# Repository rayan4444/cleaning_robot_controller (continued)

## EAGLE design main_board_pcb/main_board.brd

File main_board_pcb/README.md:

# Robodeck Main Board

## Description
Main controller for motors, sensors and other peripherals. Features:
- 1x STM32F407 100pin microcontroller
- 6x 24V-3A motor drivers with fault detection, current sensing and current limiting
    - 2 with encoder lines
    - 4 simple
- 2x 24V- 10A motor drivers with fault detection, current sensing and current limiting
- 2x N-MOSFET Switches (up to 2A)
- 1x Hall effect current sensor on main input
- 1x Input voltage measurement
- 1x UART breakout
- 1x SPI breakout
- 1x I2C breakout
- 3x pressure sensor connectors
- 1x on board temperature and humidity sensor
- 2x connectors for external temperature sensors
- 2x Cliff sensor connectors
- 1x front gap sensor connector
- 2x 5V servo connectors
- 1x SMBUS BMS connector
- 1x RS-485 transceiver
- 2x bumpers connectors
- 1x SWD programming and debug header
- 1x UI board connector
- 2x USB outputs with power and data (up to 2.5A, data can be disconnected from one of the ports)
- 2x optional breakouts for Brushless ESC (share signal with high power motor drivers)
- 1x spare port breakout

## Hardware connections
Microcontroller

|STM32 Pin | Peripheral| Signal|Notes|Test results|
|:---:|:---:|:---:|:---:|:---:|
|PC9 |**TIM3_CH4**|DRIVE1_A |PWM||
|PC12| GPIO OUT |DRIVE1_B||
|PD13| EXTI_13|DRIVE1_FAULT||  
|PB0| ADC1_CH8||DRIVE1_CURRENT||
|PB2| GPIO OUT| MOTOR_SLEEP |also BOOT1 pin|
|PC8|**TIM3_CH3**|DRIVE2_A |PWM|
|PC11|GPIO OUT|DRIVE2_B||
|PD12|EXTI_12|DRIVE2_FAULT||
|PB1| ADC_CH9|DRIVE2_CURRENT||
|PC6|**TIM3_CH1**|PRESSURE_PUMP_A|PWM|
|PA8|GPIO OUT|PRESSURE_PUMP_B||
|PD10|EXTI_10|PRESSURE_PUMP_FAULT||
|PC7|**TIM3_CH2**|CENTRAL_BRUSH_A|PWM|
|PC10|GPIO OUT|CENTRAL_BRUSH_B||
|PD11|EXTI_11|CENTRAL_BRUSH_FAULT||
|PC5|ADC1_CH5|CENTRAL_BRUSH_CURRENT||
|PE14|**TIM1_CH4**|SCRUBBER1_A|PWM|
|PE15|GPIO OUT|SCRUBBER1_B||
|PB15|EXTI_15|SCRUBBER1_FAULT||
|PA3|ADC1_CH3|SCRUBBER1_CURRENT|PWM|
|PE13|**TIM1_CH3**|SCRUBBER2_A|PWM|
|PE12|GPIO OUT|SCRUBBER2_B||   
|PB14|EXTI_14|SCRUBBER2_FAULT||
|PC4|ADC1_CH14|SCRUBBER2_CURRENT||
|PD1|EXTI_1|BUMPER1||
|PD0|EXTI_0|BUMPER2||
|PD8|EXTI_8|ENCODER1||
|PD9|EXTI_9|ENCODER2||   
|PD15|**TIM4_CH4**|SERVO1|PWM|
|PD14|**TIM4_CH3**|SERVO2|PWM|
|PB8|GPIO OUT|SOLENOID1||
|PB9|GPIO OUT|SOLENOID2||
|PE9|**TIM1_CH1**|STAINING_FAN1_A||
|PE8|GPIO OUT|STAINING_FAN1_B||
|PE6|EXTI_6|STAINING_FAN1_FAULT||
|PE11|**TIM1_CH2**|STAINING_FAN2_A||
|PE10|GPIO OUT|STAINING_FAN2_B||
|PE7|EXTI_7|STAINING_FAN2_FAULT||
|PB6|I2C1_SCL|SCL||
|PB7|i2C1_SDA|SDA||
|PD6|USART2_RX|RS485_RX||
|PD5|USART2_TX|RS485_TX||
|PE0|GPIO OUT|RS485_DIR||
|PB4|SPI1_MISO|MISO||
|PB5|SPI1_MOSI|MOSI||
|PD7|GPIO OUT|CS||
|PB3|SPI1_SCK|SCK||
|PA12|USB_DP|D_P||
|PA11|USB_DN|D_N||
|PA13|SWDIO|SWDIO||
|PA14|SWCLK|SWCLK||
|PA9|USART1_TX|USART1_TX||    
|PA10|USART1_RX|USART1_RX||
|PB11|I2C2_SDA|SMBUS_SDA||
|PB10|I2C2_SCL|SMBUS_SCL||     
|PB12|I2C2_SMBA|SMBUS_ALERT||
|PAB13|GPIO OUT|SMBUS_IO||
|PC2|ADC1_CH12|CLIFF1_OUT||
|PC3|ADC1_CH13|CLIFF2_OUT||
|PC0|ADC1_CH10|GAP_SENSE_1||
|PC1|ADC1_CH11|GAP_SENSE_2||
|PD4|EXTI_4|ONxOFF|from UI Board|
|PD3|EXTI_3|STARTxSTOP|from UI Board|
|PD2|EXTI_2|CLEANxSTAIN|from UI Board|
|PA4|DAC_1|GAP_CTL|to front gap sensor|
|PA5|DAC_2|CLIFF_CTL|to both cliff sensors|
|PC15|GPIO IN|EXT_TEMP2| DS18B20 temp sensor|  
|PC14|GPIO IN|EXT_TEMP1| DS18B20 temp sensor|  
|PA0|ADC1_CH0|PRESSURE1||
|PA6|ADC1_CH6|PRESSURE2||
|PA15|**TIM2_CH1**|BUZZER|st equivalent for tone library?|
|PA7|ADC1_CH7|PRESSURE3||GPIO OK|
|PE3|GPIO OUT|AMUX_S0|channel selection on analog mux|
|PE4|GPIO OUT|AMUX_S1|channel selection on analog mux|
|PE5|GPIO OUT|AMUX_S2|channel selection on analog mux|
|PA1|ADC1_CH1|AMUX_OUT|analog mux output|
|PA2|ADC1_CH2|LxCURRENT|current sensor output|
|PE1|GPIO OUT|SPARE_GPIO1||
|PE2|GPIO OUT|SPARE_GPIO2||

Signals from Analog Mux:

|Channel|S0/S1/S2|Signal|
|:---:|:---:|:---:|
|Y0|0/0/0|STAINING_FAN2_CURRENT|
|Y1|1/0/0|STAINING_FAN1_CURRENT|
|Y2|0/1/0|PRESSURE_PUMP_CURRENT|
|Y3|1/1/0|BAT_MEAS|
|Y4|1/0/0|-|
|Y5|1/0/1|SPARE_ANALOG1|
|Y6|1/1/0|-|
|Y7|1/1/1|SPARE_ANALOG2|

## Programming

- Using SWD: You can use a programmer (ex: Jlink or STlink) to program the baord via SWD. I included a cable with dupont wires to make it easier for you. If you have an ST development board (discovery or nucleo), you can usually re-use the STlink that is embedded on that baord to flash an external chip.

>if you are using Visual Studio Code, check out this [tutorial](https://github.com/rayan4444/vs_code_setup_tutorials/tree/master/STM32) to set up your development environment for STM32:
- Using UART: All STM32 chips come with a bootloader that lets you use UART to program them. If for some reason you don't want to use SWD to program the chip, you can still use UART. However this will require you to modify the PCB a little. In this version pin Boot 0 pulled low and pin PB2 pulled high. To use UART flashing Boot0 needs to be high and PB2 low. If needed, consult [this tutorial](http://stm32f4-discovery.net/2014/09/program-stm32f4-with-uart/)

## Errata
Manufacturing errors:
- test points names not marked on bottom silkscreen (layer missing from gerber?)
- inner layers shorted on milled slot for xt90 connector resulting in short between power and ground: to fix, saw off the milled slot on current boards. And in the future make sure to modify the library part

Errors noted when assembling:
- Pin 1 marking for analog mux is missing
- VBAT in polarity not marked on silkscreen
- XT90 connector polarity flipped (+ side on the circuit corresponds to the - side of the connector)
- Diode marking missing on FET switches
- +/-  markings missing on FET connectors
- wrong footprint for input 100uF through hole capacitor (too small)

Testing log:
- Board 0 (in shenzhen): many soldering issues. to be debugged gradually
- Board 1: 24V buck OK (5.35V, perfect), LDO OK (3.3V), Can prorgam through SWD. other peripherals not tested.
- Board 2: 24V buck OK (5.35V, perfect), LDO OK (3.3V), Can prorgam through SWD. other peripherals not tested.
- Board 3: 24V buck OK (5.38V, good), LDO OK (3.3V), Can program through SWD, other peripherals not tested.

> Some boards have burnt connectors. from debugging, sorry. one of them also has the main ninput capacitors missing, you can easily solder them up

>Note from Rayan: on all the boards I sent I did not solder the ferrite bead that connects GND and AGND because it made it easy to do basic tests. You can choose to use the ferrite bead from the BOM or short the connection with a 0 ohm resistor or some tin.

Other design errors:
- DRV8701 AVDD connected to 3.3v in V1. Make sure to disconnect AVDD from the 3.3v rail else the drivers overheat and don't work.
- Missing power on led indicator

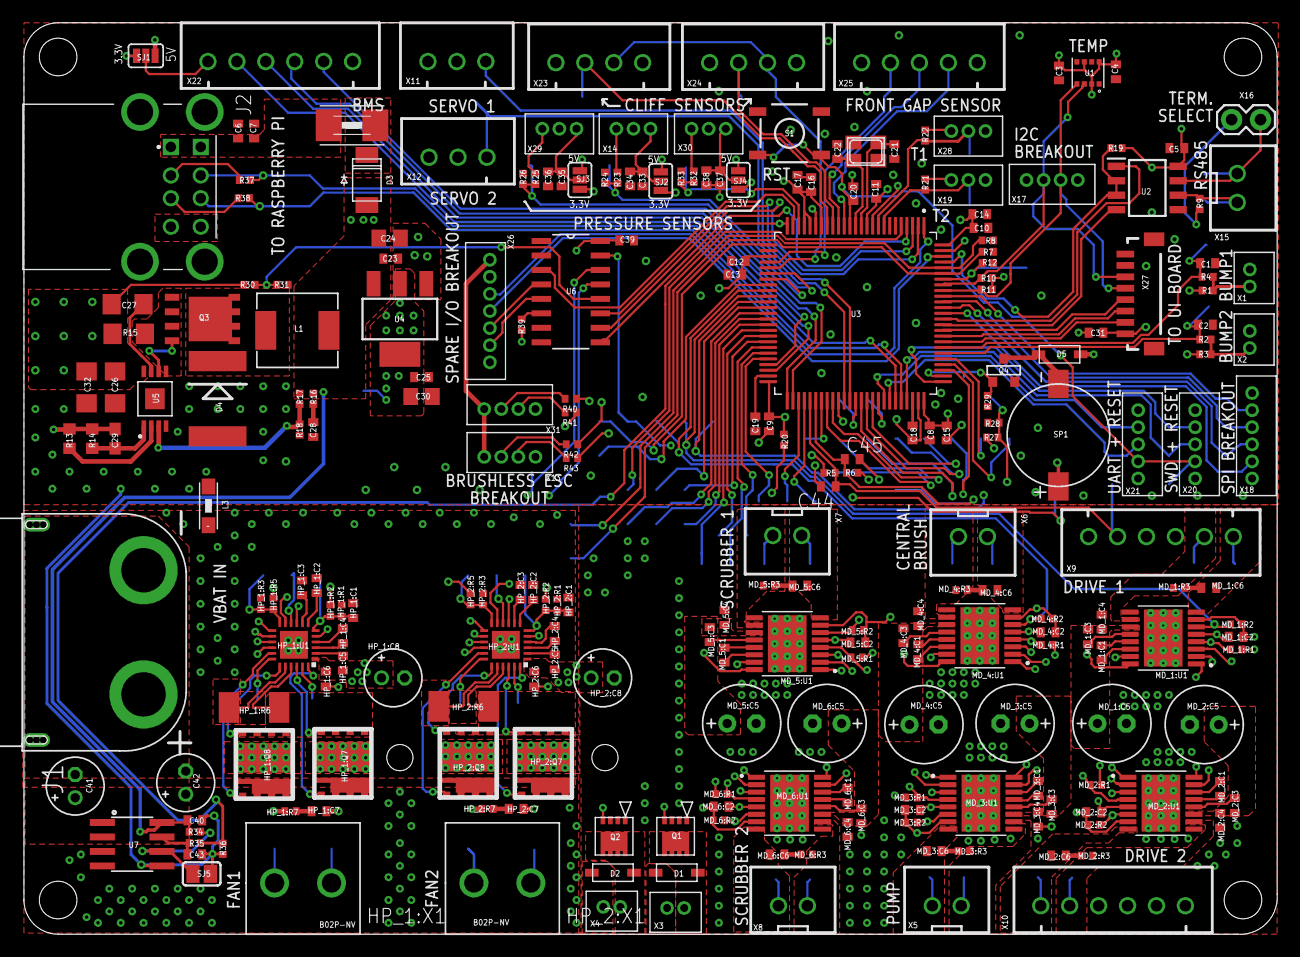
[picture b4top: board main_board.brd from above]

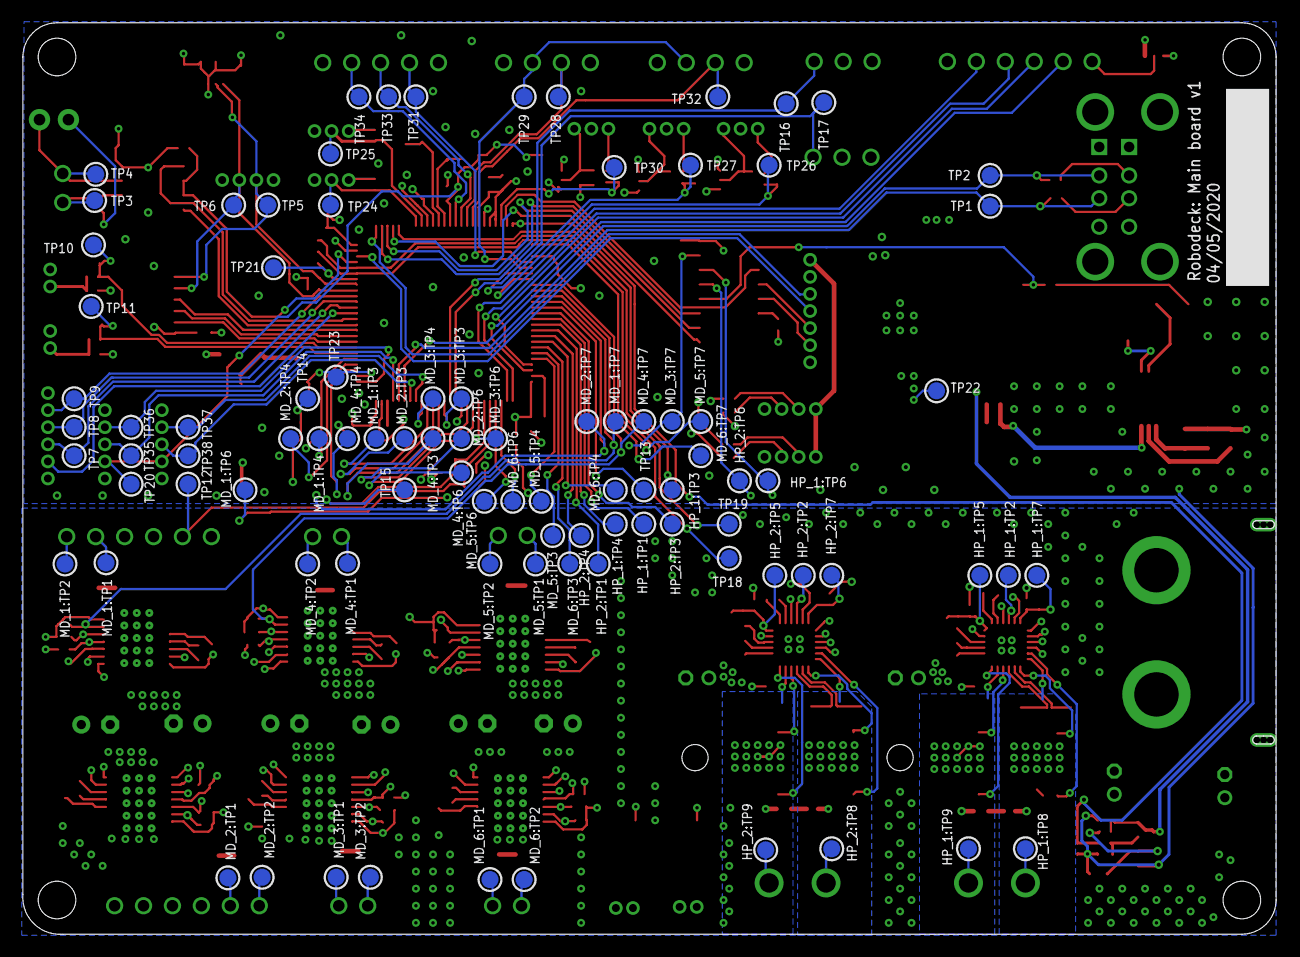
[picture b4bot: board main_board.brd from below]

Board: 4 copper layers, 110.0 x 80.0 mm, 336 parts (92 on the bottom side), 200 nets.

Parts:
C1, C2, C3, C4, C5, C8, C9, C10, C11, C12, C13, C16, C20, C23, C25, C28, C31, C33, C35, C37, C39, C40: 100nF; C0402
C6: 10uF; C0402
C7, C14, C15, C17, C34, C36, C38: 1uF; C0402
C18, C19: 2.2uF; C0402
C21, C22: 22pF; C0402
C24, C30: 10uF; C0805
C26: 47uF; C1206
C27: 0.47uF; C1206
C29: 1nF; C0603
C32: 1uF; C1206
C41: 330uF/50V; E2-5
C42: 4.7uF/50V; E2-5
C43: 10nF; C0402
C44, C45: 50pF; C0402
D1, D2: SBR3U40P1-7; SOD-123
D3: PMEG3030EP; SOD-128
D4: SK104
D5: MBR120; SOD-123
F1: TLC-MSMD250/16; 1812
HP_1:C1, HP_1:C2, HP_1:C3, HP_1:C5, HP_2:C1, HP_2:C2, HP_2:C3, HP_2:C5: 1uF; C0402
HP_1:C4, HP_1:C6, HP_2:C4, HP_2:C6: 100nF; C0402
HP_1:C7, HP_2:C7: 10nF; C0402
HP_1:C8, HP_2:C8: 4.7uF/50V; E2-5
HP_1:Q7, HP_1:Q8, HP_2:Q7, HP_2:Q8: AON6978; DFN-S-6X5-PP
HP_1:R1, HP_2:R1: 47k; R0402
HP_1:R2, HP_2:R2: 300k; R0402
HP_1:R3, HP_2:R3: DNP; R0402
HP_1:R5, HP_2:R5: 68k; R0402
HP_1:R6, HP_2:R6: 0R005; R2010
HP_1:R7, HP_2:R7: 1R; R0402
HP_1:TP1, HP_1:TP2, HP_1:TP3, HP_1:TP4, HP_1:TP5, HP_1:TP6, HP_1:TP7, HP_1:TP8, HP_1:TP9, HP_2:TP1, HP_2:TP2, HP_2:TP3, HP_2:TP4, HP_2:TP5, HP_2:TP6, HP_2:TP7, HP_2:TP8, HP_2:TP9: TESTPOINT_ROUND_1.5MM
HP_1:U1, HP_2:U1: DRV8701P; QFN24-4X4
HP_1:X1, HP_2:X1: B02P-NV
J1: XT-90-M; XT-90-M-SIDE
J2: USB_A_2; TE_1903815-1
L1: SPM6530T-4R7M
L3: WUERTH-ELEKTRONIK_1210
MD_1:C1, MD_1:C6, MD_2:C1, MD_2:C6, MD_3:C1, MD_3:C6, MD_4:C1, MD_4:C6, MD_5:C1, MD_5:C6, MD_6:C1, MD_6:C6: 22nF; C0402
MD_1:C2, MD_2:C2, MD_3:C2, MD_4:C2, MD_5:C2, MD_6:C2: 1uF; C0402
MD_1:C3, MD_1:C4, MD_2:C3, MD_2:C4, MD_3:C3, MD_3:C4, MD_4:C3, MD_4:C4, MD_5:C3, MD_5:C4, MD_6:C3, MD_6:C4: 100nF; C0402
MD_1:C5, MD_2:C5, MD_3:C5, MD_4:C5, MD_5:C5, MD_6:C5: 100uF; E2,5-7
MD_1:R1, MD_2:R1, MD_3:R1, MD_4:R1, MD_5:R1, MD_6:R1: 10k; R0402
MD_1:R2, MD_2:R2, MD_3:R2, MD_4:R2, MD_5:R2, MD_6:R2: 1.65k; R0402
MD_1:R3, MD_2:R3, MD_3:R3, MD_4:R3, MD_5:R3, MD_6:R3: 50; R0402
MD_1:TP1, MD_1:TP2, MD_1:TP3, MD_1:TP4, MD_1:TP6, MD_1:TP7, MD_2:TP1, MD_2:TP2, MD_2:TP3, MD_2:TP4, MD_2:TP6, MD_2:TP7, MD_3:TP1, MD_3:TP2, MD_3:TP3, MD_3:TP4, MD_3:TP6, MD_3:TP7, MD_4:TP1, MD_4:TP2, MD_4:TP3, MD_4:TP4, MD_4:TP6, MD_4:TP7, MD_5:TP1, MD_5:TP2, MD_5:TP3, MD_5:TP4, MD_5:TP6, MD_5:TP7, MD_6:TP1, MD_6:TP2, MD_6:TP3, MD_6:TP4, MD_6:TP6, MD_6:TP7: TESTPOINT_ROUND_1.5MM
MD_1:U1, MD_2:U1, MD_3:U1, MD_4:U1, MD_5:U1, MD_6:U1: DRV8876; IC_TPS92641PWP/NOPB
Q1, Q2: IRLHM630TRPBF; MLP8-33
Q3: SI7465DP; SI7465
Q4: DMG2302; SOT-23
R1, R2, R3, R4, R5, R6, R7, R8, R12, R17, R20, R21, R22, R29, R31, R34, R35, R39: 10k; R0402
R9: 120; R0402
R10, R11: 4.7k; R0402
R13: 40.2k; R0603
R14: 200; R0603
R15: 0.001ohm; R1206
R16: 200; R0402
R18: 3.09k; R0402
R19, R24, R26, R28, R33, R40, R41, R42, R43: DNP; R0402
R23, R25, R32: 0R; R0402
R27, R37, R38: 0; R0402
R30: 68k; R0402
R36: 20k; R0402
S1: RESET; TACTILE_SWITCH_SMD_5.2MM
SJ1, SJ2, SJ3, SJ4: SPARKFUN-PASSIVES_JUMPER_PAD-3-1&2_NC_BY_PASTE; SPARKFUN-PASSIVES_PAD-HUMPER-3-1&2_NC_BY_PASTE_YES_SILK_FUL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
SJ5: SOLDERJUMPER_REFLOW_NOPASTE
SP1: GSC9040YA-16R2700
TP1, TP2, TP3, TP4, TP5, TP6, TP7, TP8, TP9, TP10, TP11, TP12, TP13, TP14, TP15, TP16, TP17, TP18, TP19, TP20, TP21, TP22, TP23, TP24, TP25, TP26, TP27, TP28, TP29, TP30, TP31, TP32, TP33, TP34, TP35, TP36, TP37, TP38: TESTPOINT_ROUND_1.5MM
U1: BME280; PSON65P250X250X100-8N
U2: SN65HVD75DR; SOIC127P600X175-8N
U3: STM32F407VGT6; QFP50P1600X1600X160-100N
U4: AP2114H-3.3V- 1A; GEN_COMP_SOT223
U5: LM5085
U6: 74HC4051D; SOIC127P600X175-16N
U7: ACS723LLCTR-40AU (0-40A); SPARKFUN-SENSORS_SO08
X1, X2, X3, X4: B2B-ZR
X5, X6, X7, X8, X15: JST-XH-02
X9, X10, X22: JST-XH-06
X11, X12: JST-XH-03
X13, X17, X31: B4B-ZR
X14, X19, X28, X29, X30: B3B-ZR
X16: 1X02
X18: B6B-ZR
X20, X21: B5B-ZR
X23, X24: JST-XH-04
X25: JST-XH-05
X26: B7B-ZR
X27: BM08B-SRSS-TB
XTAL1: 25MHz; NX3225

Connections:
+3V3: C3.1, C4.1, C5.1, C8.1, C9.1, C10.1, C11.1, C12.1, C13.1, C14.1, C15.1, C16.1, C17.1, C25.1, C30.1, C31.2, C39.2, D5.C, HP_1:R2.2, HP_1:R5.2, HP_2:R2.2, HP_2:R5.2, MD_1:R1.2, MD_1:U1.16, MD_2:R1.2, MD_2:U1.16, MD_3:R1.2, MD_3:U1.16, MD_4:R1.2, MD_4:U1.16, MD_5:R1.2, MD_5:U1.16, MD_6:R1.2, MD_6:U1.16, R1.2, R3.2, R5.1, R6.1, R10.2, R11.2, R19.1, R20.2, R21.2, R22.2, R27.1, R39.2, SJ1.3, SJ2.3, SJ3.3, SJ4.3, SP1.P$3, TP22.P$1, U1.2, U1.6, U1.8, U2.8, U3.11, U3.19, U3.21, U3.22, U3.28, U3.50, U3.75, U3.100, U4.2, U4.4, U6.16, X9.4, X10.4, X17.1, X18.1, X19.1, X20.1, X21.1, X23.1, X24.1, X25.1, X26.6, X27.1, X28.1
+5V: C23.1, C24.1, C40.1, D3.A, L1.2, R16.2, R17.2, R34.2, SJ1.1, SJ2.1, SJ3.1, SJ4.1, U4.3, U7.8, X11.1, X12.1, X13.1, X26.7, X31.1
+24V: C26.1, C27.1, C29.2, C32.1, D1.C, D2.C, HP_1:C5.2, HP_1:C6.1, HP_1:C8.+, HP_1:Q7.P$2, HP_1:Q7.P$3, HP_1:Q7.P$4, HP_1:Q7.P$234A, HP_1:Q7.P$234B, HP_1:Q8.P$2, HP_1:Q8.P$3, HP_1:Q8.P$4, HP_1:Q8.P$234A, HP_1:Q8.P$234B, HP_1:U1.1, HP_2:C5.2, HP_2:C6.1, HP_2:C8.+, HP_2:Q7.P$2, HP_2:Q7.P$3, HP_2:Q7.P$4, HP_2:Q7.P$234A, HP_2:Q7.P$234B, HP_2:Q8.P$2, HP_2:Q8.P$3, HP_2:Q8.P$4, HP_2:Q8.P$234A, HP_2:Q8.P$234B, HP_2:U1.1, MD_1:C3.1, MD_1:C4.1, MD_1:C5.+, MD_1:U1.11, MD_2:C3.1, MD_2:C4.1, MD_2:C5.+, MD_2:U1.11, MD_3:C3.1, MD_3:C4.1, MD_3:C5.+, MD_3:U1.11, MD_4:C3.1, MD_4:C4.1, MD_4:C5.+, MD_4:U1.11, MD_5:C3.1, MD_5:C4.1, MD_5:C5.+, MD_5:U1.11, MD_6:C3.1, MD_6:C4.1, MD_6:C5.+, MD_6:U1.11, R13.1, R14.2, R15.2, R30.2, U5.8, U7.3, U7.4, X3.1, X4.1
A: R9.2, TP3.P$1, U2.6, X15.2
AGND: C41.-, C42.-, HP_1:C1.2, HP_1:C2.2, HP_1:C3.2, HP_1:C6.2, HP_1:C8.-, HP_1:R1.1, HP_1:R3.1, HP_1:R6.1, HP_1:U1.5, HP_1:U1.16, HP_1:U1.20, HP_1:U1.EXP, HP_2:C1.2, HP_2:C2.2, HP_2:C3.2, HP_2:C6.2, HP_2:C8.-, HP_2:R1.1, HP_2:R3.1, HP_2:R6.1, HP_2:U1.5, HP_2:U1.16, HP_2:U1.20, HP_2:U1.EXP, J1.2, J1.P$1, J1.P$2, J1.P$3, J1.P$4, J1.P$5, J1.P$6, L3.2, MD_1:C4.2, MD_1:C5.-, MD_1:U1.9, MD_1:U1.17, MD_1:U1.18, MD_1:U1.19, MD_1:U1.20, MD_1:U1.21, MD_1:U1.22, MD_1:U1.23, MD_1:U1.24, MD_1:U1.25, MD_1:U1.26, MD_1:U1.27, MD_1:U1.28, MD_1:U1.29, MD_1:U1.30, MD_1:U1.31, MD_1:U1.32, MD_2:C4.2, MD_2:C5.-, MD_2:U1.9, MD_2:U1.17, MD_2:U1.18, MD_2:U1.19, MD_2:U1.20, MD_2:U1.21, MD_2:U1.22, MD_2:U1.23, MD_2:U1.24, MD_2:U1.25, MD_2:U1.26, MD_2:U1.27, MD_2:U1.28, MD_2:U1.29, MD_2:U1.30, MD_2:U1.31, MD_2:U1.32, MD_3:C4.2, MD_3:C5.-, MD_3:U1.9, MD_3:U1.17, MD_3:U1.18, MD_3:U1.19, MD_3:U1.20, MD_3:U1.21, MD_3:U1.22, MD_3:U1.23, MD_3:U1.24, MD_3:U1.25, MD_3:U1.26, MD_3:U1.27, MD_3:U1.28, MD_3:U1.29, MD_3:U1.30, MD_3:U1.31, MD_3:U1.32, MD_4:C4.2, MD_4:C5.-, MD_4:U1.9, MD_4:U1.17, MD_4:U1.18, MD_4:U1.19, MD_4:U1.20, MD_4:U1.21, MD_4:U1.22, MD_4:U1.23, MD_4:U1.24, MD_4:U1.25, MD_4:U1.26, MD_4:U1.27, MD_4:U1.28, MD_4:U1.29, MD_4:U1.30, MD_4:U1.31, MD_4:U1.32, MD_5:C4.2, MD_5:C5.-, MD_5:U1.9, MD_5:U1.17, MD_5:U1.18, MD_5:U1.19, MD_5:U1.20, MD_5:U1.21, MD_5:U1.22, MD_5:U1.23, MD_5:U1.24, MD_5:U1.25, MD_5:U1.26, MD_5:U1.27, MD_5:U1.28, MD_5:U1.29, MD_5:U1.30, MD_5:U1.31, MD_5:U1.32, MD_6:C4.2, MD_6:C5.-, MD_6:U1.9, MD_6:U1.17, MD_6:U1.18, MD_6:U1.19, MD_6:U1.20, MD_6:U1.21, MD_6:U1.22, MD_6:U1.23, MD_6:U1.24, MD_6:U1.25, MD_6:U1.26, MD_6:U1.27, MD_6:U1.28, MD_6:U1.29, MD_6:U1.30, MD_6:U1.31, MD_6:U1.32, Q1.S1, Q1.S2, Q1.S3, Q2.S1, Q2.S2, Q2.S3
AMUX_OUT: U3.24, U6.3
AMUX_S0: U3.2, U6.11
AMUX_S1: U3.3, U6.10
AMUX_S2: U3.4, U6.9
B: TP4.P$1, U2.7, X15.1, X16.2
BAT_IN: C41.+, C42.+, J1.1, U7.1, U7.2
BAT_MEAS: R30.1, R31.2, U6.12
BUMPER1: C1.1, R4.2, TP10.P$1, U3.82
BUMPER2: C2.1, R2.2, TP11.P$1, U3.81
BUZZER: Q4.G, R29.1, TP23.P$1, U3.77
CENTRAL_BRUSH_A: MD_4:TP3.P$1, MD_4:U1.1, U3.64
CENTRAL_BRUSH_B: MD_4:TP4.P$1, MD_4:U1.2, U3.78
CENTRAL_BRUSH_CURRENT: MD_4:R2.1, MD_4:TP7.P$1, MD_4:U1.6, U3.34
CENTRAL_BRUSH_FAULT: MD_4:R1.1, MD_4:TP6.P$1, MD_4:U1.4, U3.58
CLEAN/STAIN: U3.83, X27.2
CLIFF1_OUT: TP28.P$1, U3.17, X24.2
CLIFF2_OUT: TP32.P$1, U3.18, X23.2
CLIFF_CTL: TP29.P$1, U3.30, X23.3, X24.3
CS: U3.88, X18.5
DRIVE1_A: MD_1:TP3.P$1, MD_1:U1.1, U3.66
DRIVE1_B: MD_1:TP4.P$1, MD_1:U1.2, U3.80
DRIVE1_CURRENT: MD_1:R2.1, MD_1:TP7.P$1, MD_1:U1.6, U3.35
DRIVE1_FAULT: MD_1:R1.1, MD_1:TP6.P$1, MD_1:U1.4, U3.60
DRIVE1_OUT_A: MD_1:C6.1, MD_1:TP2.P$1, MD_1:U1.8, X9.1
DRIVE1_OUT_B: MD_1:R3.2, MD_1:TP1.P$1, MD_1:U1.10, X9.2
DRIVE2_A: MD_2:TP3.P$1, MD_2:U1.1, U3.65
DRIVE2_B: MD_2:TP4.P$1, MD_2:U1.2, U3.79
DRIVE2_CURRENT: MD_2:R2.1, MD_2:TP7.P$1, MD_2:U1.6, U3.36
DRIVE2_FAULT: MD_2:R1.1, MD_2:TP6.P$1, MD_2:U1.4, U3.59
DRIVE2_OUT_A: MD_2:C6.1, MD_2:TP2.P$1, MD_2:U1.8, X10.1
DRIVE2_OUT_B: MD_2:R3.2, MD_2:TP1.P$1, MD_2:U1.10, X10.2
D_N: J2.6, R37.1, TP2.P$1, U3.70
D_P: J2.7, R38.1, TP1.P$1, U3.71
ENCODER1: C44.1, R5.2, TP12.P$1, U3.55, X9.5
ENCODER2: C45.1, R6.2, TP15.P$1, U3.56, X10.5
EXT_TEMP1: R21.1, TP24.P$1, U3.8, X19.2
EXT_TEMP2: R22.1, TP25.P$1, U3.9, X28.2
GAP_CTL: TP31.P$1, U3.29, X25.2
GAP_SENSE_1: TP34.P$1, U3.15, X25.4
GAP_SENSE_2: TP33.P$1, U3.16, X25.3
GND: C1.2, C2.2, C3.2, C4.2, C5.2, C6.1, C7.1, C8.2, C9.2, C10.2, C11.2, C12.2, C13.2, C14.2, C15.2, C16.2, C17.2, C18.2, C19.2, C20.2, C21.1, C22.1, C23.2, C24.2, C25.2, C26.2, C28.1, C30.2, C31.1, C32.2, C33.2, C34.2, C35.2, C36.2, C37.2, C38.2, C39.1, C40.2, C43.2, C44.2, C45.2, D4.1, J2.4, J2.8, J2.P1, J2.P2, J2.P3, J2.P4, L3.1, MD_1:C2.2, MD_1:R2.2, MD_1:U1.7, MD_1:U1.15, MD_2:C2.2, MD_2:R2.2, MD_2:U1.7, MD_2:U1.15, MD_3:C2.2, MD_3:R2.2, MD_3:U1.7, MD_3:U1.15, MD_4:C2.2, MD_4:R2.2, MD_4:U1.7, MD_4:U1.15, MD_5:C2.2, MD_5:R2.2, MD_5:U1.7, MD_5:U1.15, MD_6:C2.2, MD_6:R2.2, MD_6:U1.7, MD_6:U1.15, Q4.S, R7.2, R8.2, R12.1, R18.1, R24.1, R26.1, R28.2, R29.2, R31.1, R33.1, R36.1, S1.3, S1.4, SJ5.2, U1.1, U1.5, U1.7, U2.5, U3.10, U3.20, U3.27, U3.74, U3.99, U4.1, U5.4, U5.9, U6.7, U6.8, U7.5, X1.2, X2.2, X9.3, X10.3, X11.2, X12.2, X13.4, X14.2, X17.4, X18.6, X19.3, X20.5, X21.5, X22.6, X23.4, X24.4, X25.5, X26.1, X27.7, X27.8, X28.3, X29.2, X30.2, X31.4, XTAL1.2, XTAL1.4
HP_1:!OC: HP_1:TP2.P$1, HP_1:U1.10
HP_1:ACT4_DRIVE+: HP_1:Q8.P$9, HP_1:R7.2, HP_1:TP8.P$1, HP_1:U1.18, HP_1:X1.1
HP_1:ACT4_DRIVE-: HP_1:C7.1, HP_1:Q7.P$9, HP_1:TP9.P$1, HP_1:U1.23, HP_1:X1.2
HP_1:AVDD: HP_1:C2.1, HP_1:U1.7
HP_1:N$4: HP_1:Q8.P$8, HP_1:U1.19
HP_1:N$40: HP_1:C4.1, HP_1:U1.3
HP_1:N$41: HP_1:C4.2, HP_1:U1.4
HP_1:N$44: HP_1:Q7.P$5, HP_1:Q7.P$6, HP_1:Q7.P$7, HP_1:Q8.P$5, HP_1:Q8.P$6, HP_1:Q8.P$7, HP_1:R6.2, HP_1:U1.21
HP_1:N$45: HP_1:R3.2, HP_1:R5.1, HP_1:TP7.P$1, HP_1:U1.12
HP_1:N$46: HP_1:Q7.P$8, HP_1:U1.22
HP_1:N$49: HP_1:C5.1, HP_1:U1.2
HP_1:N$50: HP_1:C3.1, HP_1:U1.8
HP_1:N$52: HP_1:Q8.P$1, HP_1:U1.17
HP_1:N$53: HP_1:Q7.P$1, HP_1:U1.24
HP_1:N$77: HP_1:C7.2, HP_1:R7.1
HP_1:VREF: HP_1:C1.1, HP_1:R1.2, HP_1:R2.1, HP_1:TP5.P$1, HP_1:U1.6
HP_2:!OC: HP_2:TP2.P$1, HP_2:U1.10
HP_2:ACT4_DRIVE+: HP_2:Q8.P$9, HP_2:R7.2, HP_2:TP8.P$1, HP_2:U1.18, HP_2:X1.1
HP_2:ACT4_DRIVE-: HP_2:C7.1, HP_2:Q7.P$9, HP_2:TP9.P$1, HP_2:U1.23, HP_2:X1.2
HP_2:AVDD: HP_2:C2.1, HP_2:U1.7
HP_2:N$4: HP_2:Q8.P$8, HP_2:U1.19
HP_2:N$40: HP_2:C4.1, HP_2:U1.3
HP_2:N$41: HP_2:C4.2, HP_2:U1.4
HP_2:N$44: HP_2:Q7.P$5, HP_2:Q7.P$6, HP_2:Q7.P$7, HP_2:Q8.P$5, HP_2:Q8.P$6, HP_2:Q8.P$7, HP_2:R6.2, HP_2:U1.21
HP_2:N$45: HP_2:R3.2, HP_2:R5.1, HP_2:TP7.P$1, HP_2:U1.12
HP_2:N$46: HP_2:Q7.P$8, HP_2:U1.22
HP_2:N$49: HP_2:C5.1, HP_2:U1.2
HP_2:N$50: HP_2:C3.1, HP_2:U1.8
HP_2:N$52: HP_2:Q8.P$1, HP_2:U1.17
HP_2:N$53: HP_2:Q7.P$1, HP_2:U1.24
HP_2:N$77: HP_2:C7.2, HP_2:R7.1
HP_2:VREF: HP_2:C1.1, HP_2:R1.2, HP_2:R2.1, HP_2:TP5.P$1, HP_2:U1.6
L-CURRENT: R35.1, R36.2, U3.25
MD_1:N$1: MD_1:C1.2, MD_1:U1.14
MD_1:N$2: MD_1:C1.1, MD_1:U1.13
MD_1:N$3: MD_1:C3.2, MD_1:U1.12
MD_1:N$4: MD_1:C6.2, MD_1:R3.1
MD_2:N$1: MD_2:C1.2, MD_2:U1.14
MD_2:N$2: MD_2:C1.1, MD_2:U1.13
MD_2:N$3: MD_2:C3.2, MD_2:U1.12
MD_2:N$4: MD_2:C6.2, MD_2:R3.1
MD_3:N$1: MD_3:C1.2, MD_3:U1.14
MD_3:N$2: MD_3:C1.1, MD_3:U1.13
MD_3:N$3: MD_3:C3.2, MD_3:U1.12
MD_3:N$4: MD_3:C6.2, MD_3:R3.1
MD_4:N$1: MD_4:C1.2, MD_4:U1.14
MD_4:N$2: MD_4:C1.1, MD_4:U1.13
MD_4:N$3: MD_4:C3.2, MD_4:U1.12
MD_4:N$4: MD_4:C6.2, MD_4:R3.1
MD_5:N$1: MD_5:C1.2, MD_5:U1.14
MD_5:N$2: MD_5:C1.1, MD_5:U1.13
MD_5:N$3: MD_5:C3.2, MD_5:U1.12
MD_5:N$4: MD_5:C6.2, MD_5:R3.1
MD_6:N$1: MD_6:C1.2, MD_6:U1.14
MD_6:N$2: MD_6:C1.1, MD_6:U1.13
MD_6:N$3: MD_6:C3.2, MD_6:U1.12
MD_6:N$4: MD_6:C6.2, MD_6:R3.1
MISO: TP8.P$1, U3.90, X18.3
MOSI: TP9.P$1, U3.91, X18.2
MOTOR_SLEEP: HP_1:U1.13, HP_2:U1.13, MD_1:U1.3, MD_2:U1.3, MD_3:U1.3, MD_4:U1.3, MD_5:U1.3, MD_6:U1.3, R20.1, TP13.P$1, U3.37
M_VREF: MD_1:C2.1, MD_1:U1.5, MD_2:C2.1, MD_2:U1.5, MD_3:C2.1, MD_3:U1.5, MD_4:C2.1, MD_4:U1.5, MD_5:C2.1, MD_5:U1.5, MD_6:C2.1, MD_6:U1.5, R27.2, R28.1, TP14.P$1
unnamed: R2.1, R3.1, X2.1
unnamed: MD_3:C6.1, MD_3:TP2.P$1, MD_3:U1.8, X5.1
unnamed: R1.1, R4.1, X1.1
unnamed: MD_3:R3.2, MD_3:TP1.P$1, MD_3:U1.10, X5.2
unnamed: MD_5:C6.1, MD_5:TP2.P$1, MD_5:U1.8, X7.1
unnamed: MD_5:R3.2, MD_5:TP1.P$1, MD_5:U1.10, X7.2
unnamed: MD_6:C6.1, MD_6:TP2.P$1, MD_6:U1.8, X8.1
unnamed: MD_6:R3.2, MD_6:TP1.P$1, MD_6:U1.10, X8.2
unnamed: MD_4:C6.1, MD_4:TP2.P$1, MD_4:U1.8, X6.1
unnamed: MD_4:R3.2, MD_4:TP1.P$1, MD_4:U1.10, X6.2
unnamed: D2.A, Q2.D1, Q2.D2, Q2.D3, Q2.D4, Q2.DRAIN0, X4.2
unnamed: D1.A, Q1.D1, Q1.D2, Q1.D3, Q1.D4, Q1.DRAIN0, X3.2
unnamed: R9.1, X16.1
unnamed: C18.1, U3.73
unnamed: C19.1, U3.49
unnamed: R12.2, TP21.P$1, U3.94
unnamed: SJ1.2, X22.1
unnamed: D3.K, F1.1
unnamed: D5.A, Q4.D, SP1.P$2
unnamed: R23.2, X14.1
unnamed: C33.1, C34.1, SJ2.2, X14.3
unnamed: R25.2, X29.1
unnamed: C28.2, R16.1
unnamed: C35.1, C36.1, SJ3.2, X29.3
unnamed: R32.2, X30.1
unnamed: C37.1, C38.1, SJ4.2, X30.3
unnamed: R13.2, U5.2
unnamed: C43.1, R35.2, U7.7
unnamed: J2.2, R37.2
unnamed: J2.3, R38.2
unnamed: R34.1, SJ5.1, U7.6
unnamed: R42.2, X13.2
unnamed: R39.1, U6.6
unnamed: R43.2, X13.3
unnamed: R40.2, X31.2
unnamed: R41.2, X31.3
unnamed: Q3.1, Q3.2, Q3.3, R15.1, U5.5
unnamed: C29.1, R14.1, U5.1
unnamed: R17.1, R18.2, U5.3
unnamed: C27.2, U5.7
unnamed: D4.2, L1.1, Q3.5, Q3.6, Q3.7, Q3.8, Q3.9
unnamed: Q3.4, U5.6
ON/OFF: U3.85, X27.4
PRESSURE1: R32.1, R33.2, TP30.P$1, U3.23
PRESSURE2: R23.1, R24.2, TP27.P$1, U3.31
PRESSURE3: R25.1, R26.2, TP26.P$1, U3.32
PRESSURE_PUMP_A: MD_3:TP3.P$1, MD_3:U1.1, U3.63
PRESSURE_PUMP_B: MD_3:TP4.P$1, MD_3:U1.2, U3.67
PRESSURE_PUMP_CURRENT: MD_3:R2.1, MD_3:TP7.P$1, MD_3:U1.6, U6.15
PRESSURE_PUMP_FAULT: MD_3:R1.1, MD_3:TP6.P$1, MD_3:U1.4, U3.57
RESET: C20.1, S1.1, S1.2, TP20.P$1, U3.14, X20.4, X21.4
RS485_DIR: R19.2, U2.2, U2.3, U3.97
RS485_RX: U2.1, U3.87
RS485_TX: U2.4, U3.86
SCK: TP7.P$1, U3.89, X18.4
SCL: R11.1, TP6.P$1, U1.4, U3.92, X17.2, X27.5
SCRUBBER1_A: MD_5:TP3.P$1, MD_5:U1.1, U3.45
SCRUBBER1_B: MD_5:TP4.P$1, MD_5:U1.2, U3.46
SCRUBBER1_CURRENT: MD_5:R2.1, MD_5:TP7.P$1, MD_5:U1.6, U3.26
SCRUBBER1_FAULT: MD_5:R1.1, MD_5:TP6.P$1, MD_5:U1.4, U3.54
SCRUBBER2_A: MD_6:TP3.P$1, MD_6:U1.1, U3.44
SCRUBBER2_B: MD_6:TP4.P$1, MD_6:U1.2, U3.43
SCRUBBER2_CURRENT: MD_6:R2.1, MD_6:TP7.P$1, MD_6:U1.6, U3.33
SCRUBBER2_FAULT: MD_6:R1.1, MD_6:TP6.P$1, MD_6:U1.4, U3.53
SDA: R10.1, TP5.P$1, U1.3, U3.93, X17.3, X27.6
SERVO1: TP16.P$1, U3.62, X11.3
SERVO2: TP17.P$1, U3.61, X12.3
SMBUS_ALERT: U3.51, X22.4
SMBUS_IO: U3.52, X22.5
SMBUS_SCL: U3.47, X22.3
SMBUS_SDA: U3.48, X22.2
SOLENOID1: Q1.GATE, R7.1, TP18.P$1, U3.95
SOLENOID2: Q2.GATE, R8.1, TP19.P$1, U3.96
SPARE_ANALOG1: U6.5, X26.2
SPARE_ANALOG2: U6.4, X26.3
SPARE_GPIO1: U3.98, X26.4
SPARE_GPIO2: U3.1, X26.5
STAINING_FAN1_A: HP_1:TP4.P$1, HP_1:U1.15, R40.1, U3.40
STAINING_FAN1_B: HP_1:TP1.P$1, HP_1:U1.14, U3.39
STAINING_FAN1_CURRENT: HP_1:TP6.P$1, HP_1:U1.11, U6.14
STAINING_FAN1_FAULT: HP_1:TP3.P$1, HP_1:U1.9, R41.1, U3.5
STAINING_FAN2_A: HP_2:TP4.P$1, HP_2:U1.15, R42.1, U3.42
STAINING_FAN2_B: HP_2:TP1.P$1, HP_2:U1.14, U3.41
STAINING_FAN2_CURRENT: HP_2:TP6.P$1, HP_2:U1.11, U6.13
STAINING_FAN2_FAULT: HP_2:TP3.P$1, HP_2:U1.9, R43.1, U3.38
START/STOP: U3.84, X27.3
SWCLK: TP36.P$1, U3.76, X20.2
SWDIO: TP35.P$1, U3.72, X20.3
USART1_RX: TP38.P$1, U3.69, X21.3
USART1_TX: TP37.P$1, U3.68, X21.2
VUSB: C6.2, C7.2, F1.2, J2.1, J2.5
X_N: C22.2, U3.13, XTAL1.3
X_P: C21.2, U3.12, XTAL1.1

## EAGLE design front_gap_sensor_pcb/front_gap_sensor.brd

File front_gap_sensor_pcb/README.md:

# Robodeck Front gap sensor

## Description
This small board features two TCRT5000 sensors and a votlage controlled current source to control the brightness of the IR LEDs in the sensors if needed/wanted. 

## Hardware connections 
Connections marked on the board.

In constant current mode: 
- Solder a resistor on R1 and R3 to set the current 
- Solder JP1 and JP2 to GND

In controlled current mode: 
- Connect CLIFF_CTRL signal to an analog voltage source (ex: STM32 DAC)
- Solder a 0 ohm resistor to R1 and R3
- Solder JP1 and JP2 to CTRL

>Note: the current source feeds both analog sensors together, not individually. 

## Errata
Errors noted when assembling: 
- nothing to note

Testing log:
- Not tested yet

## Open Issues

|Date|Issue|Responsible|Status|
|:---:|:---:|:---:|:---:|
|17.6.2020|In the current schematics, R1&R3 value should be 57.6Ω|||
|10.07.2020|Change componenets as per the below image|||
|20.07.2020|Seperate the TX+2xRX from the board via a dedicated connector|||
|20.07.2020|Future: merge the gap sensor electronics into the mainboard||||

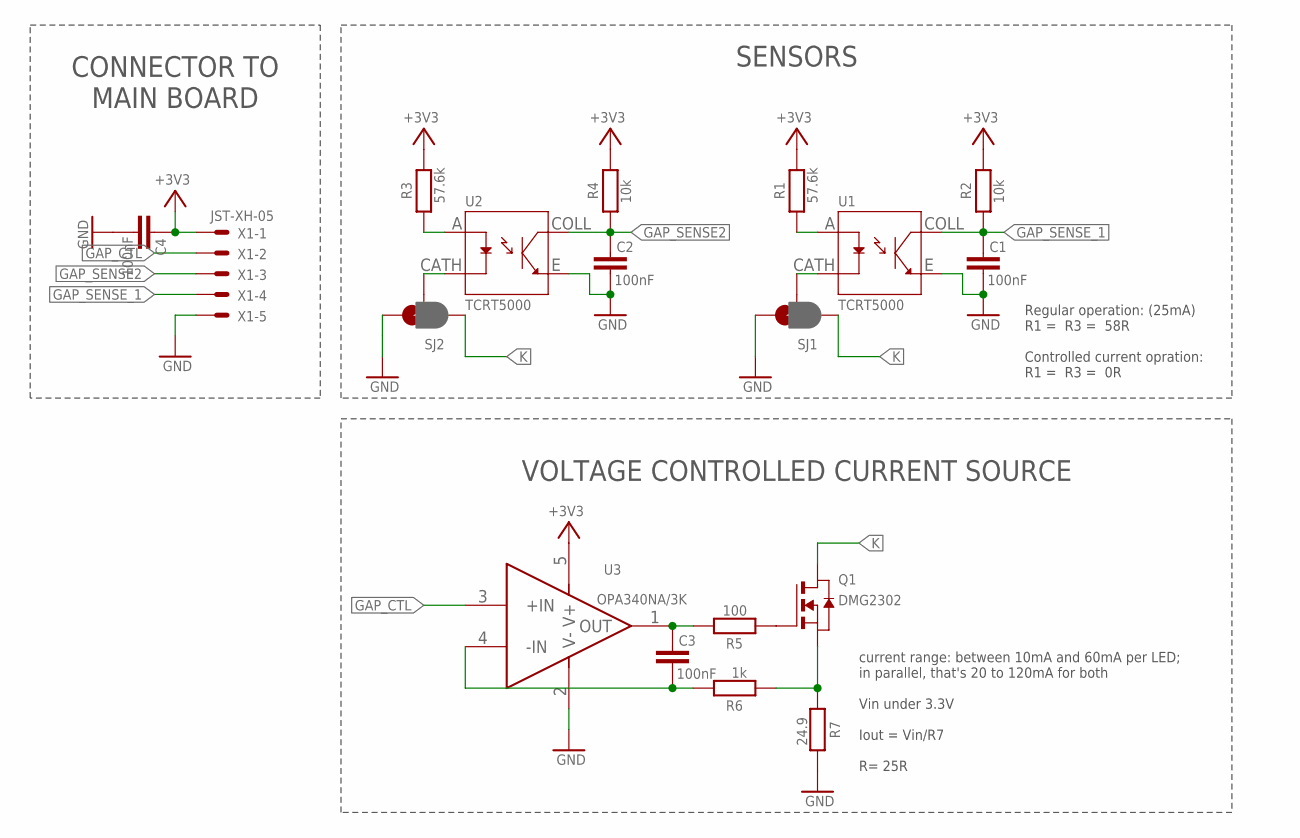
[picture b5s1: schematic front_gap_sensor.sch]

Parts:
C1, C2, C3, C4: 100nF; C0402
Q1: DMG2302; SOT-23
R1, R3: 57.6k; R0402
R2, R4: 10k; R0402
R5: 100; R0402
R6: 1k; R0402
R7: 24.9; R0402
SJ1, SJ2: SPARKFUN-PASSIVES_JUMPER_PAD-3-1&2_NC_BY_PASTE; SPARKFUN-PASSIVES_PAD-HUMPER-3-1&2_NC_BY_PASTE_YES_SILK_FUL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
U1, U2: TCRT5000; OPTO_TCRT5000
U3: OPA340NA/3K; SOT95P280X145-5N
X1: JST-XH-05; JST-XH-05-PACKAGE-ROUND-PAD

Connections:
+3V3: C4.2, R1.2, R2.2, R3.2, R4.2, U3.5 (V+), X1.1
GAP_CTL: U3.3 (+IN), X1.2
GAP_SENSE2: C2.2, R4.1, U2.COLL, X1.3
GAP_SENSE_1: C1.2, R2.1, U1.COLL, X1.4
GND: C1.1, C2.1, C4.1, R7.2, SJ1.3, SJ2.3, U1.E, U2.E, U3.2 (V-), X1.5
K: Q1.D, SJ1.1, SJ2.1
K_1: SJ2.2, U2.CATH
unnamed: SJ1.2, U1.CATH
unnamed: C3.2, R5.2, U3.1 (OUT)
unnamed: C3.1, R6.2, U3.4 (-IN)
unnamed: Q1.G, R5.1
unnamed: Q1.S, R6.1, R7.1
S_IN1: R3.1, U2.A
S_IN2: R1.1, U1.A

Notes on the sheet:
Regular operation: (25mA) R1 = R3 = 58R Controlled current opration: R1 = R3 = 0R
SENSORS
CONNECTOR TO MAIN BOARD
VOLTAGE CONTROLLED CURRENT SOURCE
current range: between 10mA and 60mA per LED; in parallel, that's 20 to 120mA for both Vin under 3.3V Iout = Vin/R7 R= 25R

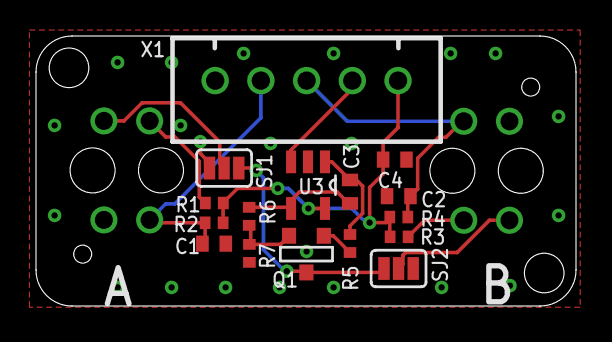
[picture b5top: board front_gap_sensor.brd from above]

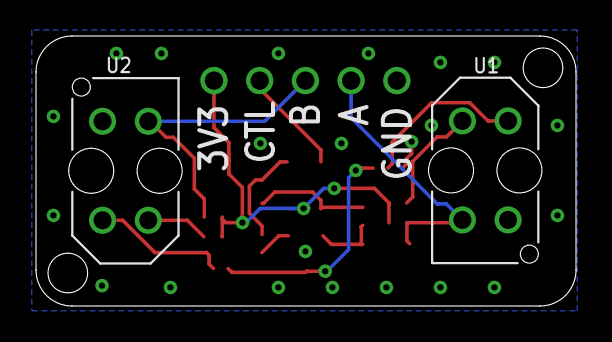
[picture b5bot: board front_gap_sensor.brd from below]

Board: 2 copper layers, 30.0 x 15.0 mm, 18 parts (2 on the bottom side), 14 nets.

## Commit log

2020-08-13 Post project commit
2020-08-13 documentation assets
